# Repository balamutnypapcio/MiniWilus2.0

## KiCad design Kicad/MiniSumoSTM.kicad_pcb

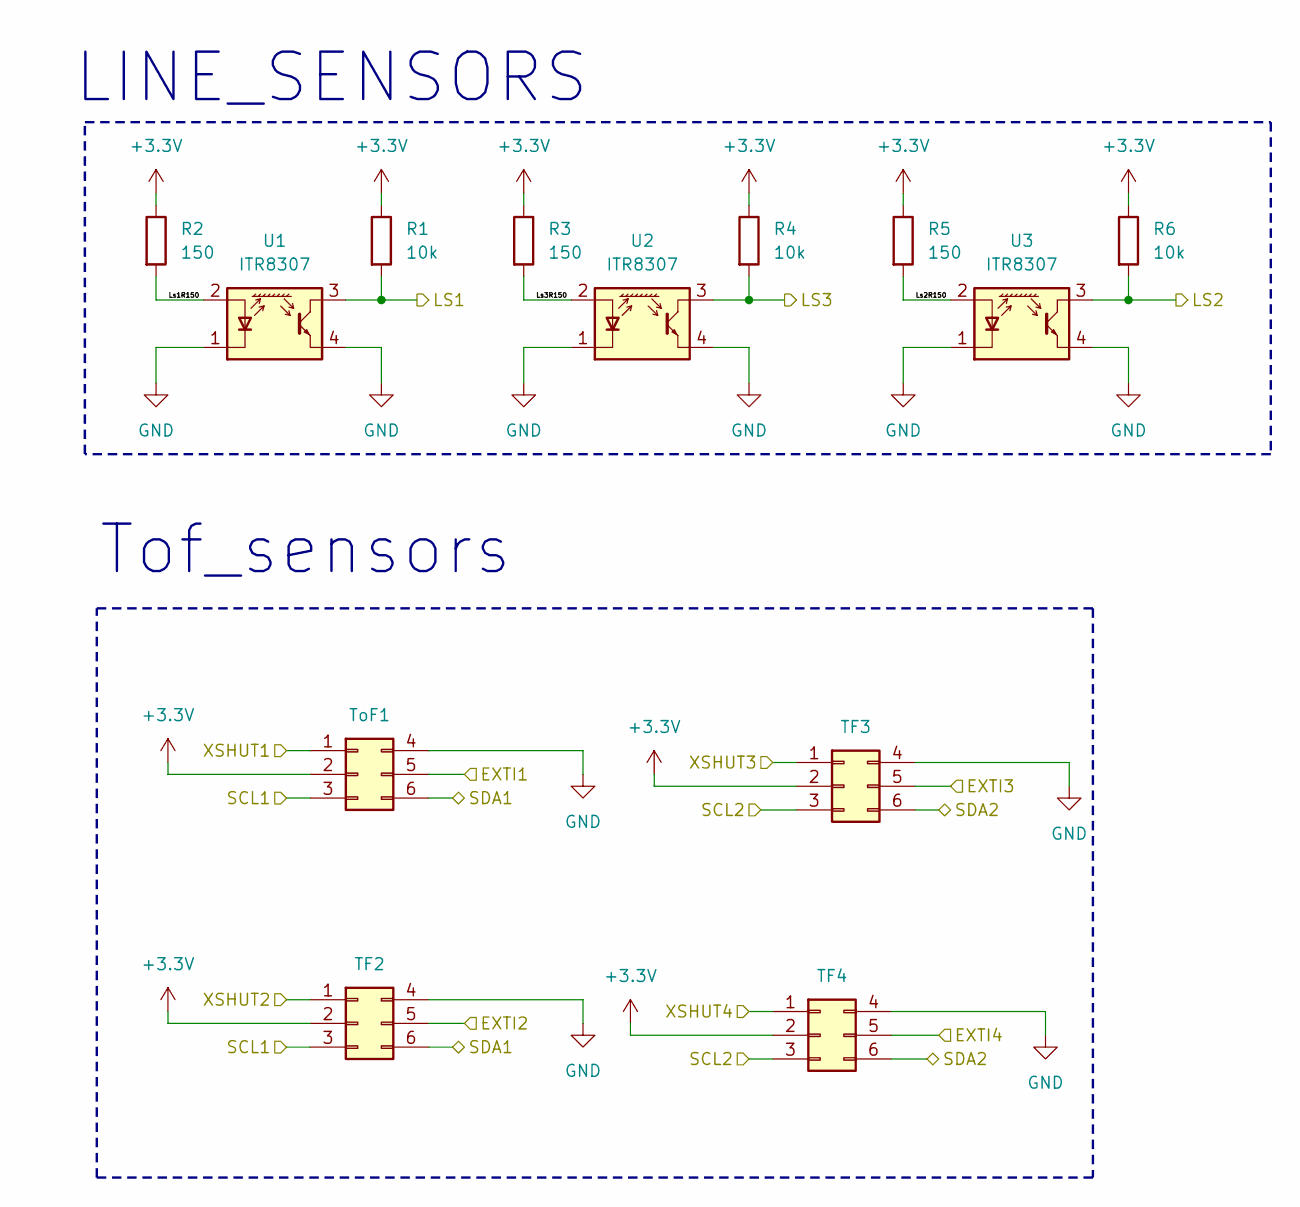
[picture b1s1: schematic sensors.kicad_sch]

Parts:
R1, R4, R6: 10k; R_0805_2012Metric_Pad1.20x1.40mm_HandSolder
R2, R3, R5: 150; R_0805_2012Metric_Pad1.20x1.40mm_HandSolder
TF2, TF3, TF4: Conn_02x03_Top_Bottom; PinHeader_2x03_P2.54mm_Vertical
ToF1: Conn_02x03_Top_Bottom; PinHeader_2x03_P2.54mm_Vertical
U1, U2, U3: ITR8307; Everlight_ITR8307

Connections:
+3.3V: R1.1, R2.1, R3.1, R4.1, R5.1, R6.1, TF2.2, TF3.2, TF4.2, ToF1.2; also elsewhere on the board
/MCU/EXTI1: ToF1.5; also elsewhere on the board
/MCU/EXTI2: TF2.5; also elsewhere on the board
/MCU/EXTI3: TF3.5; also elsewhere on the board
/MCU/EXTI4: TF4.5; also elsewhere on the board
/MCU/LS1: R1.2, U1.3 (C); also elsewhere on the board
/MCU/LS2: R6.2, U3.3 (C); also elsewhere on the board
/MCU/LS3: R4.2, U2.3 (C); also elsewhere on the board
/MCU/SCL1: TF2.3, ToF1.3; also elsewhere on the board
/MCU/SCL2: TF3.3, TF4.3; also elsewhere on the board
/MCU/SDA1: TF2.6, ToF1.6; also elsewhere on the board
/MCU/SDA2: TF3.6, TF4.6; also elsewhere on the board
/MCU/XSHUT1: ToF1.1; also elsewhere on the board
/MCU/XSHUT2: TF2.1; also elsewhere on the board
/MCU/XSHUT3: TF3.1; also elsewhere on the board
/MCU/XSHUT4: TF4.1; also elsewhere on the board
/sensors/Ls1R150: R2.2, U1.2 (A)
/sensors/Ls2R150: R5.2, U3.2 (A)
/sensors/Ls3R150: R3.2, U2.2 (A)
GND: TF2.4, TF3.4, TF4.4, ToF1.4, U1.1 (K), U1.4 (E), U2.1 (K), U2.4 (E), U3.1 (K), U3.4 (E); also elsewhere on the board

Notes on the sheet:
Tof_sensors
LINE_SENSORS

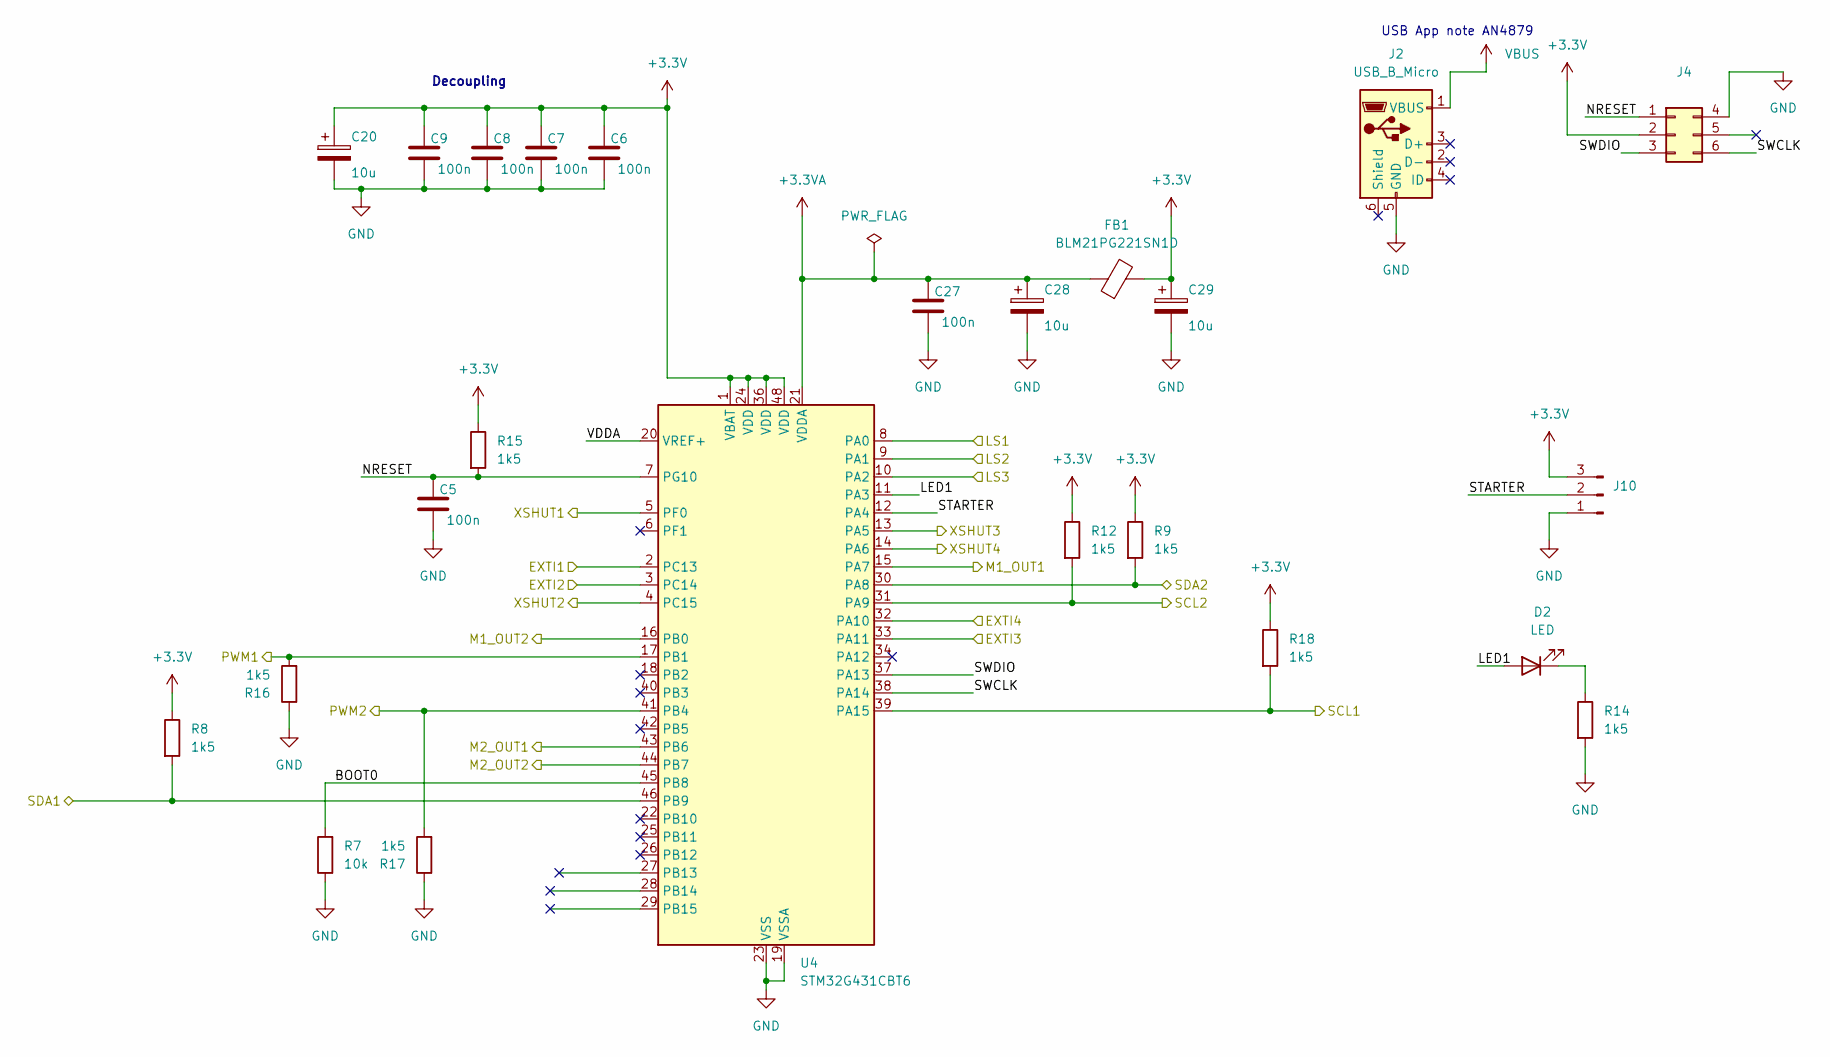
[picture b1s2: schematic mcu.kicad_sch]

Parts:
C5, C6, C7, C8, C9, C27: 100n; C_0805_2012Metric_Pad1.18x1.45mm_HandSolder
C20, C28, C29: 10u; CP_EIA-3528-12_Kemet-T_HandSolder
D2: LED; LED_0805_2012Metric_Pad1.15x1.40mm_HandSolder
FB1: BLM21PG221SN1D; C_0805_2012Metric_Pad1.18x1.45mm_HandSolder
J2: USB_B_Micro; USB_Micro-B_Amphenol_10118194-0001LF_Horizontal
J4: Conn_02x03_Top_Bottom; PinHeader_2x03_P2.54mm_Vertical
J10: Conn_01x03_Pin; PinHeader_1x03_P2.54mm_Vertical
R7: 10k; R_0805_2012Metric_Pad1.20x1.40mm_HandSolder
R8, R9, R12, R14, R15, R16, R17, R18: 1k5; R_0805_2012Metric_Pad1.20x1.40mm_HandSolder
U4: STM32G431CBT6; LQFP-48_7x7mm_P0.5mm

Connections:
+3.3V: C6.1, C7.1, C8.1, C9.1, C20.1, C29.1, FB1.2, J4.2, J10.3, R8.1, R9.1, R12.1, R15.1, R18.1, U4.1 (VBAT), U4.24 (VDD), U4.36 (VDD), U4.48 (VDD); also elsewhere on the board
+3.3VA: C27.1, C28.1, FB1.1, U4.21 (VDDA)
/MCU/BOOT0: R7.2, U4.45 (PB8)
/MCU/EXTI1: U4.2 (PC13); also elsewhere on the board
/MCU/EXTI2: U4.3 (PC14); also elsewhere on the board
/MCU/EXTI3: U4.33 (PA11); also elsewhere on the board
/MCU/EXTI4: U4.32 (PA10); also elsewhere on the board
/MCU/LED1: D2.2 (A), U4.11 (PA3)
/MCU/LS1: U4.8 (PA0); also elsewhere on the board
/MCU/LS2: U4.9 (PA1); also elsewhere on the board
/MCU/LS3: U4.10 (PA2); also elsewhere on the board
/MCU/M1_OUT1: U4.15 (PA7); also elsewhere on the board
/MCU/M1_OUT2: U4.16 (PB0); also elsewhere on the board
/MCU/M2_OUT1: U4.43 (PB6); also elsewhere on the board
/MCU/M2_OUT2: U4.44 (PB7); also elsewhere on the board
/MCU/NRESET: C5.1, J4.1, R15.2, U4.7 (PG10)
/MCU/PWM1: R16.2, U4.17 (PB1); also elsewhere on the board
/MCU/PWM2: R17.2, U4.41 (PB4); also elsewhere on the board
/MCU/SCL1: R18.2, U4.39 (PA15); also elsewhere on the board
/MCU/SCL2: R12.2, U4.31 (PA9); also elsewhere on the board
/MCU/SDA1: R8.2, U4.46 (PB9); also elsewhere on the board
/MCU/SDA2: R9.2, U4.30 (PA8); also elsewhere on the board
/MCU/STARTER: J10.2, U4.12 (PA4)
/MCU/SWCLK: J4.6, U4.38 (PA14)
/MCU/SWDIO: J4.3, U4.37 (PA13)
/MCU/VDDA: U4.20 (VREF+)
/MCU/XSHUT1: U4.5 (PF0); also elsewhere on the board
/MCU/XSHUT2: U4.4 (PC15); also elsewhere on the board
/MCU/XSHUT3: U4.13 (PA5); also elsewhere on the board
/MCU/XSHUT4: U4.14 (PA6); also elsewhere on the board
GND: C5.2, C6.2, C7.2, C8.2, C9.2, C20.2, C27.2, C28.2, C29.2, J2.5 (GND), J4.4, J10.1, R7.1, R14.2, R16.1, R17.1, U4.19 (VSSA), U4.23 (VSS), U4.35 (VSS), U4.47 (VSS); also elsewhere on the board
unnamed: D2.1 (K), R14.1
VBUS: J2.1 (VBUS); also elsewhere on the board

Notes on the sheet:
Decoupling
USB App note AN4879

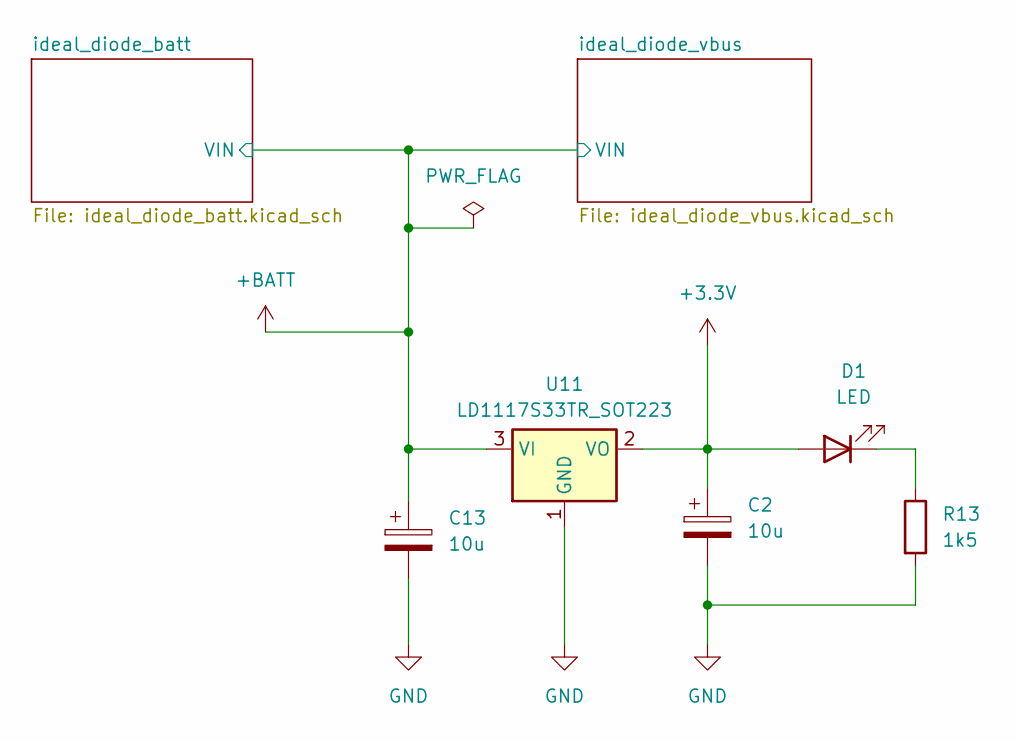
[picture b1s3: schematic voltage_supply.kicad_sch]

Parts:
C2, C13: 10u; CP_EIA-3528-12_Kemet-T_HandSolder
D1: LED; LED_0805_2012Metric_Pad1.15x1.40mm_HandSolder
R13: 1k5; R_0805_2012Metric_Pad1.20x1.40mm_HandSolder
U11: LD1117S33TR_SOT223; SOT-223-3_TabPin2

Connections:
+3.3V: C2.1, D1.2 (A), U11.2 (VO); also elsewhere on the board
+BATT: C13.1, U11.3 (VI); also elsewhere on the board
GND: C2.2, C13.2, R13.2, U11.1 (GND); also elsewhere on the board
unnamed: D1.1 (K), R13.1

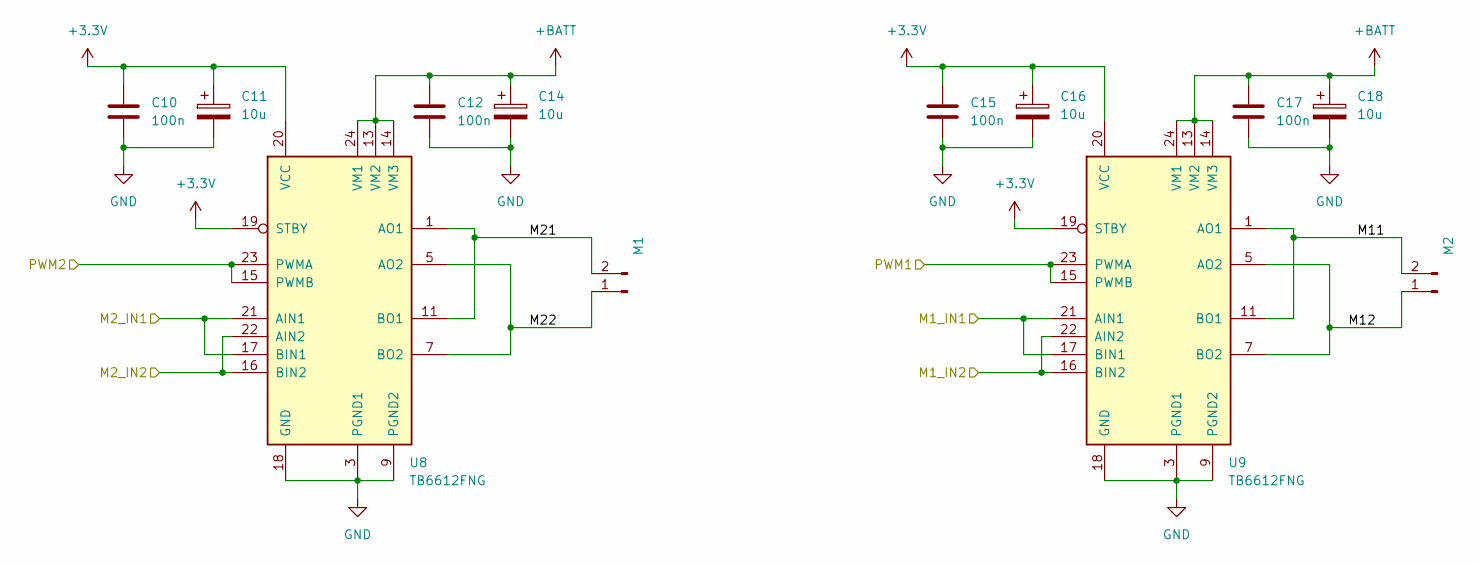
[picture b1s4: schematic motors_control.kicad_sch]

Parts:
C10, C12, C15, C17: 100n; C_0805_2012Metric_Pad1.18x1.45mm_HandSolder
C11, C14, C16, C18: 10u; CP_EIA-3528-12_Kemet-T_HandSolder
M1, M2: Conn_01x02_Pin; PinSocket_1x02_P2.54mm_Vertical
U8, U9: TB6612FNG; SSOP-24_5.3x8.2mm_P0.65mm

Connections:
+3.3V: C10.1, C11.1, C15.1, C16.1, U8.19 (STBY), U8.20 (VCC), U9.19 (STBY), U9.20 (VCC); also elsewhere on the board
+BATT: C12.1, C14.1, C17.1, C18.1, U8.13 (VM2), U8.14 (VM3), U8.24 (VM1), U9.13 (VM2), U9.14 (VM3), U9.24 (VM1); also elsewhere on the board
/MCU/M1_OUT1: U9.17 (BIN1), U9.21 (AIN1); also elsewhere on the board
/MCU/M1_OUT2: U9.16 (BIN2), U9.22 (AIN2); also elsewhere on the board
/MCU/M2_OUT1: U8.17 (BIN1), U8.21 (AIN1); also elsewhere on the board
/MCU/M2_OUT2: U8.16 (BIN2), U8.22 (AIN2); also elsewhere on the board
/MCU/PWM1: U9.15 (PWMB), U9.23 (PWMA); also elsewhere on the board
/MCU/PWM2: U8.15 (PWMB), U8.23 (PWMA); also elsewhere on the board
GND: C10.2, C11.2, C12.2, C14.2, C15.2, C16.2, C17.2, C18.2, U8.3 (PGND1), U8.4 (PGND1), U8.9 (PGND2), U8.10 (PGND2), U8.18 (GND), U9.3 (PGND1), U9.4 (PGND1), U9.9 (PGND2), U9.10 (PGND2), U9.18 (GND); also elsewhere on the board

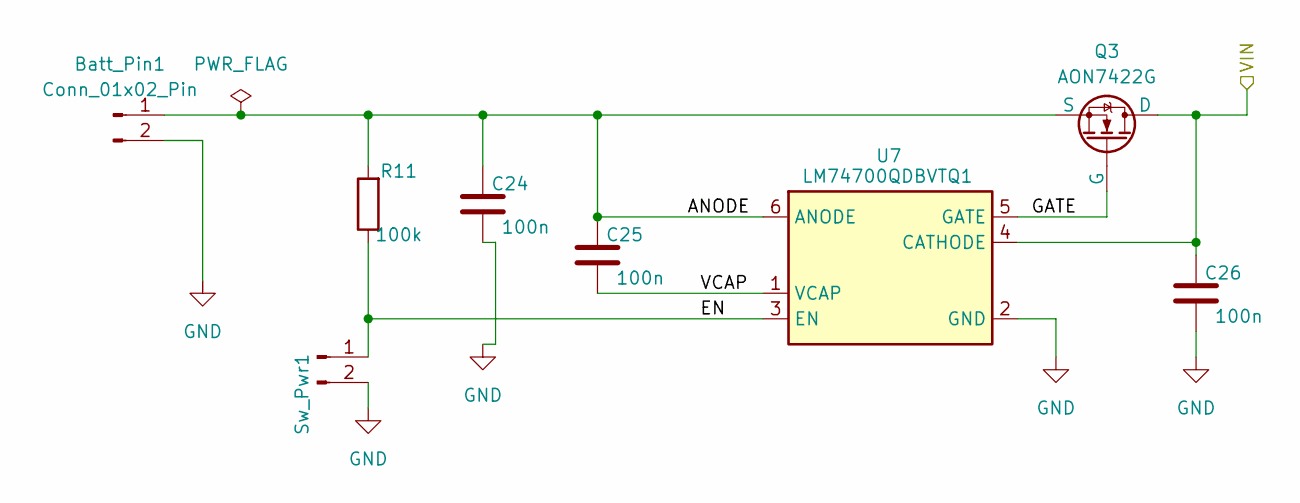
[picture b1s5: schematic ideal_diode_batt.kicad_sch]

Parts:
Batt_Pin1: Conn_01x02_Pin; PinSocket_1x02_P2.54mm_Vertical
C24, C25, C26: 100n; C_0805_2012Metric_Pad1.18x1.45mm_HandSolder
Q3: AON7422G; DFN-8-1EP_3x3mm_P0.5mm_EP1.7x2.4mm
R11: 100k; R_0805_2012Metric_Pad1.20x1.40mm_HandSolder
Sw_Pwr1: Conn_01x02_Pin; PinSocket_1x02_P2.54mm_Vertical
U7: LM74700QDBVTQ1; SOT-23-6_Handsoldering

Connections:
+BATT: C26.1, Q3.5 (D), Q3.6 (D), Q3.7 (D), Q3.8 (D), Q3.9 (D), U7.4 (CATHODE); also elsewhere on the board
/voltage_supply/ideal_diode_batt/ANODE: Batt_Pin1.1, C24.1, C25.1, Q3.1 (S), Q3.2 (S), Q3.3 (S), R11.2, U7.6 (ANODE)
/voltage_supply/ideal_diode_batt/EN: R11.1, Sw_Pwr1.1, U7.3 (EN)
/voltage_supply/ideal_diode_batt/GATE: Q3.4 (G), U7.5 (GATE)
/voltage_supply/ideal_diode_batt/VCAP: C25.2, U7.1 (VCAP)
GND: Batt_Pin1.2, C24.2, C26.2, Sw_Pwr1.2, U7.2 (GND); also elsewhere on the board

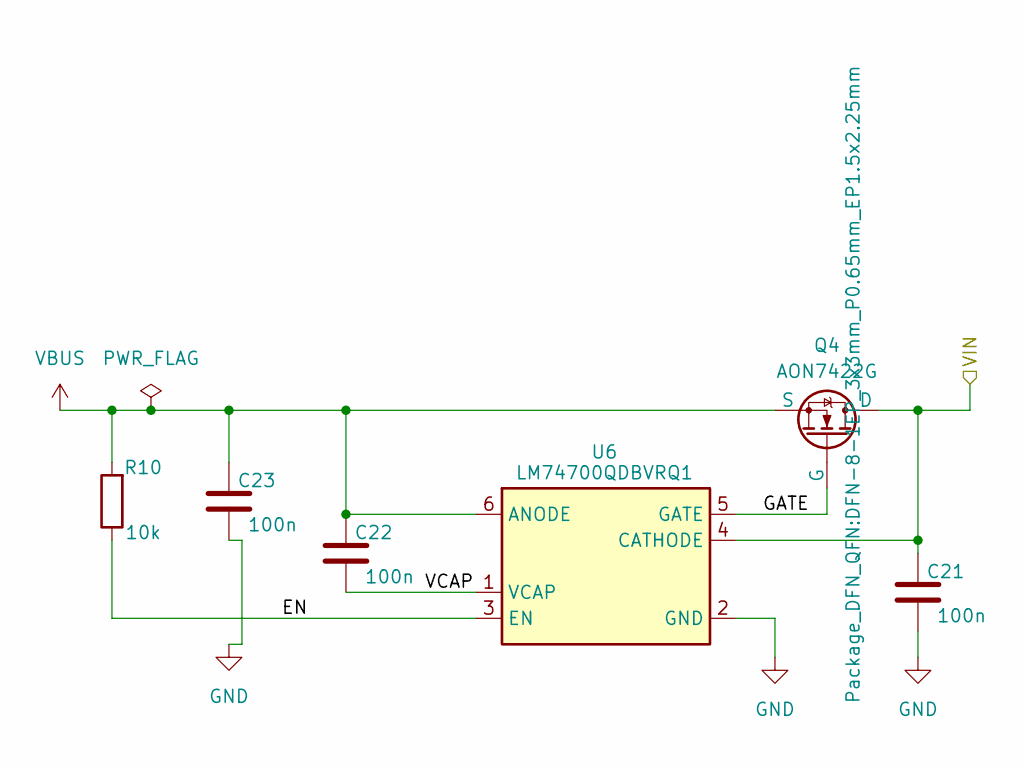
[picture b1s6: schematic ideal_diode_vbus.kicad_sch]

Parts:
C21, C22, C23: 100n; C_0805_2012Metric_Pad1.18x1.45mm_HandSolder
Q4: AON7422G; DFN-8-1EP_3x3mm_P0.65mm_EP1.5x2.25mm
R10: 10k; R_0805_2012Metric_Pad1.20x1.40mm_HandSolder
U6: LM74700QDBVRQ1; SOT-23-6_Handsoldering

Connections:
+BATT: C21.1, Q4.5 (D), Q4.6 (D), Q4.7 (D), Q4.8 (D), Q4.9 (D), U6.4 (CATHODE); also elsewhere on the board
/voltage_supply/ideal_diode_vbus/EN: R10.1, U6.3 (EN)
/voltage_supply/ideal_diode_vbus/GATE: Q4.4 (G), U6.5 (GATE)
/voltage_supply/ideal_diode_vbus/VCAP: C22.2, U6.1 (VCAP)
GND: C21.2, C23.2, U6.2 (GND); also elsewhere on the board
VBUS: C22.1, C23.1, Q4.1 (S), Q4.2 (S), Q4.3 (S), R10.2, U6.6 (ANODE); also elsewhere on the board

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
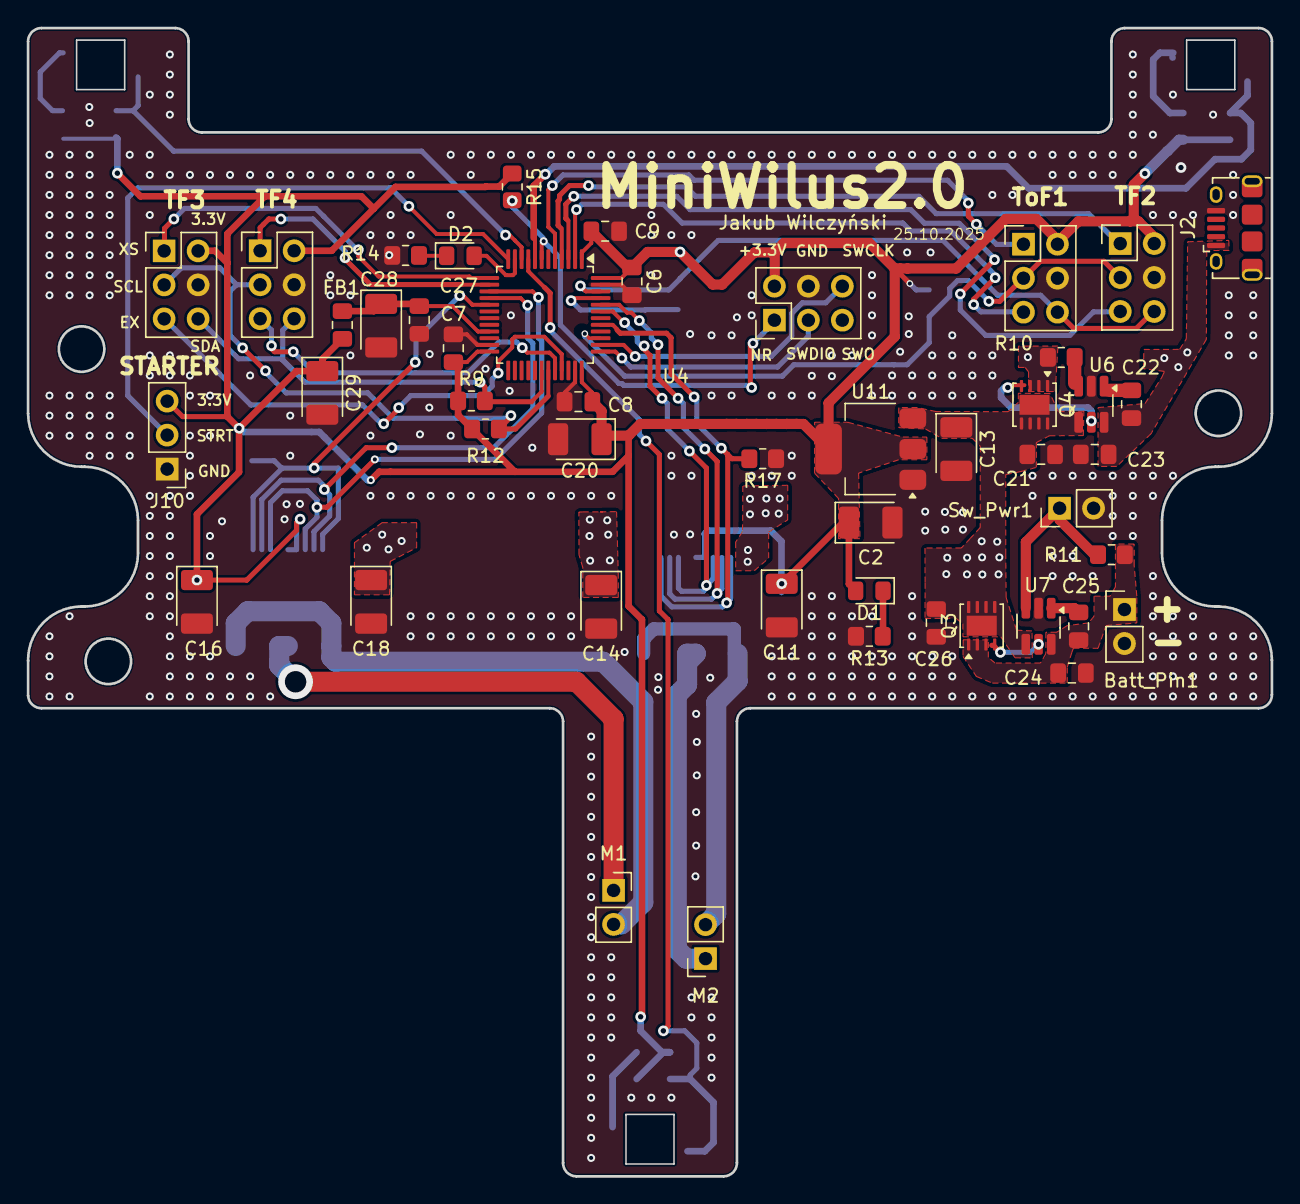
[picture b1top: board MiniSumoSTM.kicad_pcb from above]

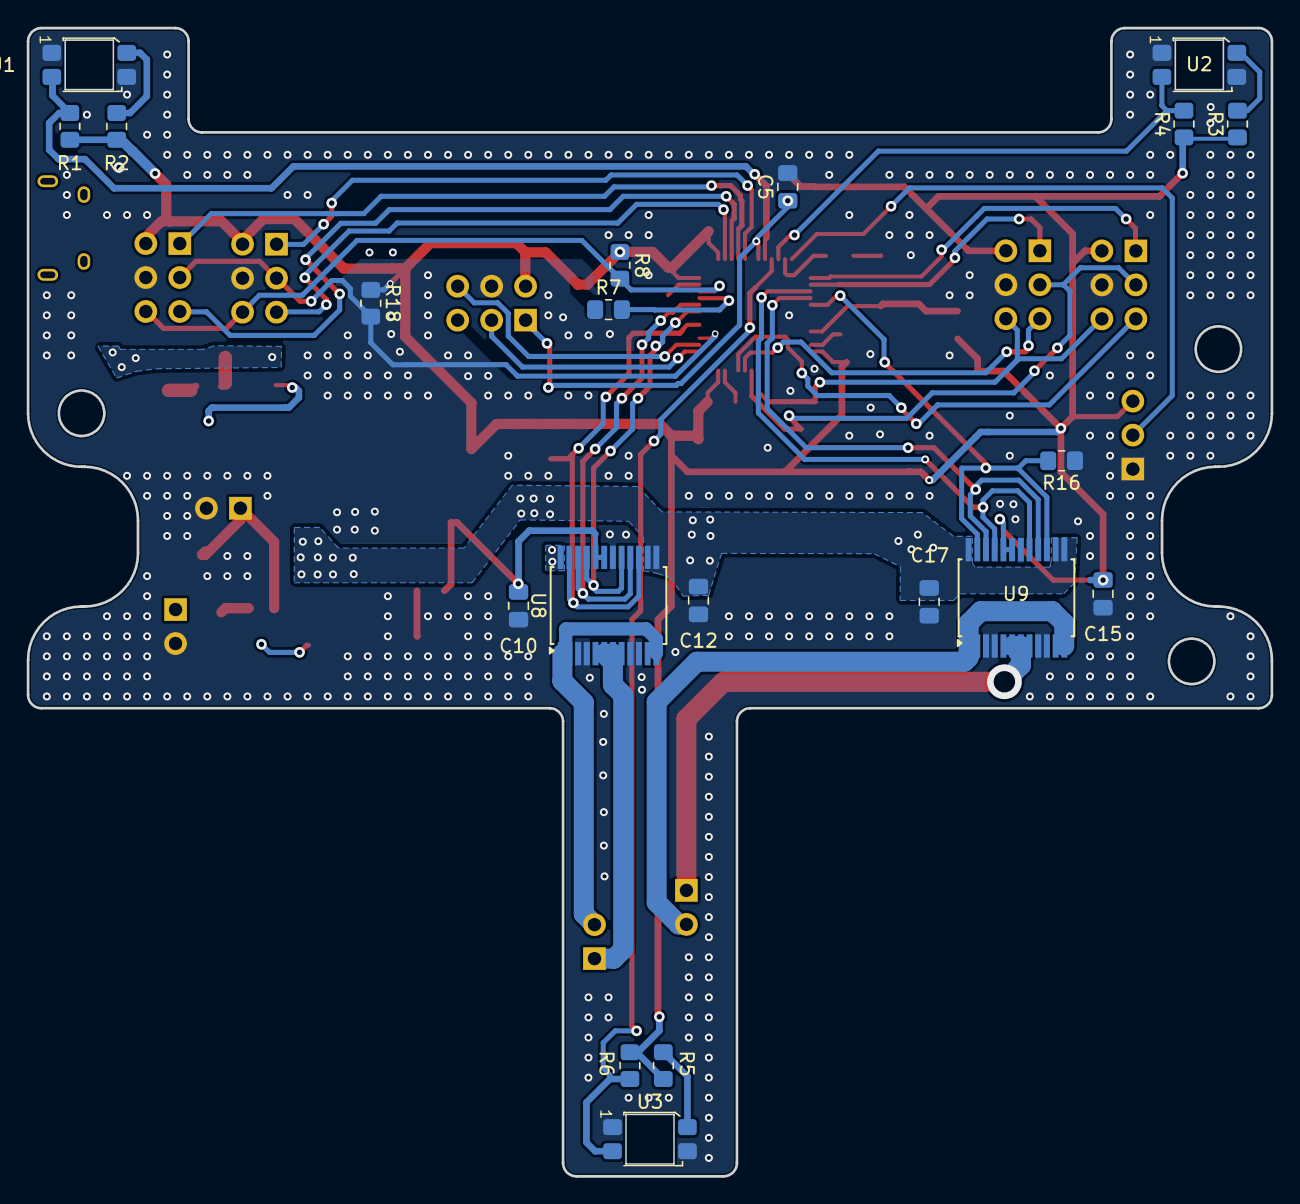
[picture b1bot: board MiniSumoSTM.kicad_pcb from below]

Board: 2 copper layers, 93.0 x 85.8 mm, 68 parts (20 on the bottom side), 48 nets.

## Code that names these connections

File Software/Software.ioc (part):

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Mcu.Name=STM32G431C(6-8-B)Tx
Mcu.Package=LQFP48
Mcu.UserName=STM32G431CBTx
PA0.Mode=IN1-Single-Ended
PA0.Signal=ADC1_IN1
PA1.Mode=IN2-Single-Ended
PA1.Signal=ADC1_IN2
PA10.GPIOParameters=GPIO_Label
PA10.GPIO_Label=EXTI4
PA10.Signal=GPXTI10
PA11.GPIOParameters=GPIO_Label
PA11.GPIO_Label=EXTI3
PA11.Signal=GPXTI11
PA13.Mode=Serial_Wire
PA13.Signal=SYS_JTMS-SWDIO
PA14.Mode=Serial_Wire
PA14.Signal=SYS_JTCK-SWCLK
PA15.Mode=I2C
PA15.Signal=I2C1_SCL
PA2.Mode=IN3-Single-Ended
PA2.Signal=ADC1_IN3
PA3.GPIOParameters=GPIO_Label
PA3.GPIO_Label=LED
PA3.Signal=GPIO_Output
PA4.GPIOParameters=GPIO_Label
PA4.GPIO_Label=STARTER
PA4.Signal=GPIO_Output
PA5.GPIOParameters=GPIO_Label
PA5.GPIO_Label=XSHUT3
PA5.Signal=GPIO_Output
PA6.GPIOParameters=GPIO_Label
PA6.GPIO_Label=XSHUT4
PA6.Signal=GPIO_Output
PA7.GPIOParameters=GPIO_Label
PA7.GPIO_Label=M1_OUT1
PA7.Signal=GPIO_Output
PA8.Mode=I2C
PA8.Signal=I2C2_SDA
PA9.Mode=I2C
PA9.Signal=I2C2_SCL
PB0.GPIOParameters=GPIO_Label
PB0.GPIO_Label=M1_OUT2
PB0.Signal=GPIO_Output
PB1.GPIOParameters=GPIO_Label
PB1.GPIO_Label=PWM1
PB1.Signal=S_TIM3_CH4
PB4.GPIOParameters=GPIO_Label
PB4.GPIO_Label=PWM2
PB4.Signal=S_TIM3_CH1
PB6.GPIOParameters=GPIO_Label
PB6.GPIO_Label=M2_OUT1
PB6.Signal=GPIO_Output
PB7.GPIOParameters=GPIO_Label
PB7.GPIO_Label=M2_OUT2
PB7.Signal=GPIO_Output
PB9.Mode=I2C
PB9.Signal=I2C1_SDA
PC13.GPIOParameters=GPIO_Label
PC13.GPIO_Label=EXTI1
PC13.Signal=GPXTI13
PC14-OSC32_IN.GPIOParameters=GPIO_Label
PC14-OSC32_IN.GPIO_Label=EXTI2
PC14-OSC32_IN.Signal=GPXTI14
PC15-OSC32_OUT.GPIOParameters=GPIO_Label
PC15-OSC32_OUT.GPIO_Label=XSHUT2
PC15-OSC32_OUT.Signal=GPIO_Output
PF0-OSC_IN.GPIOParameters=GPIO_Label
PF0-OSC_IN.GPIO_Label=XSHUT1
PF0-OSC_IN.Signal=GPIO_Output
RCC.HSE_VALUE=8000000
RCC.SYSCLKFreq_VALUE=170000000
RCC.SYSCLKSource=RCC_SYSCLKSOURCE_PLLCLK
board=custom

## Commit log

2025-10-21 finished pcb
2025-10-25 finished pcb - added pwm resistors, and fixed VDDA decoupling
2025-10-25 change mounting hole
2025-10-26 deleted worng pcb
2025-10-26 not small changes
2025-11-11 nic nie działa
2025-11-13 Delay not working
2025-11-15 tof 1,2 work
2025-11-16 tofs 1,2,3,4 work well
2025-11-20 fixed bug with tofs in interuptrs
2025-11-22 small commit
2025-11-26 tofs works
2025-12-12 fixed scheme with i2c
2025-12-13 work IR but with every button
2025-12-13 fixed pcb
2025-12-13 commit before - fixed start module, in kicad fix -- pcb with new scl1 route and boot0
2025-12-16 kicad schemas documentation
